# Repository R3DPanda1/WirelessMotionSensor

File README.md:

# Wireless Motion Sensor

A portable all-in-one motion sensor device with Bluetooth connectivity and SD card data logging capabilities, developed as a Bachelor's thesis project at UAS Technikum Wien.

## Overview

This project presents a low-cost, user-friendly wireless motion tracking device designed for measuring acceleration, rotation, and orientation data at 100 Hz using a Bosch BNO055 IMU sensor. The device features wireless communication between two units, local data storage, and an intuitive OLED display interface.

## Key Features

- **High-Speed Motion Capture**: Measures acceleration, rotation, and orientation at 100 Hz
- **Wireless Communication**: Bluetooth Classic connectivity for real-time data sharing between two devices
- **Data Logging**: SD card storage in CSV format for easy data access
- **Clock Synchronization**: Devices can be synchronized by tapping them together (high-g interrupt method)
- **User-Friendly Interface**: 1.3" OLED display with push-button controls
- **Portable Design**: Battery-powered with 3D-printed snap-fit case
- **Multiple Operation Modes**:
  - Fusion Mode (orientation visualization)
  - Temperature Mode
  - Spirit Level Mode
  - Raw Readings Mode

## Hardware Components

### Main Components
- **Microcontroller**: ESP32-WROOM-32
- **IMU Sensor**: Bosch BNO055 (9-DOF with sensor fusion)
- **Display**: SH1106 1.3" OLED (128x64 pixels)
- **Storage**: MicroSD card slot
- **Power**: Li-Ion/Li-Polymer battery with USB-C charging
- **Connectivity**: Bluetooth Classic

### PCB Design

The custom 4-layer PCB features:
- Compact design (96.6mm x 44.4mm x 19.9mm)
- Hand-assembled components
- Compatible with various 0.96" or 1.3" OLED displays
- M5 mounting holes for case integration

### Circuit Schematic

## Case Design

The device is housed in a 3D-printed snap-fit case designed in Autodesk Fusion:

Features:
- Snap-fit assembly (no screws required)
- Integrated battery compartment
- Button and switch caps
- Multi-material printing support for labeling

## Software Architecture

The firmware uses FreeRTOS with seven concurrent tasks:
- **Button Task**: Handles user input
- **Sensor Task**: Reads IMU data and manages clock synchronization
- **Render Task**: Controls OLED display output
- **Bluetooth TX/RX Tasks**: Manages wireless communication
- **SD Card Task**: Handles file operations
- **CSV Task**: Prepares data for logging with write buffer optimization

### Data Recording

- CSV format for easy accessibility
- Buffered writing to reduce SD card wear
- Simultaneous local and remote data logging
- Timestamp synchronization between devices

## Operation Modes

1. **Fusion Mode**: 3D cube visualization of orientation with linear acceleration graph
2. **Temperature Mode**: Display local and remote temperature readings
3. **Spirit Level Mode**: Digital level indicator with tilt angle
4. **Raw Readings Mode**: Real-time graphs of accelerometer, gyroscope, and magnetometer data
5. **Clock Sync Mode**: Synchronize device clocks by tapping them together

## Getting Started

### Hardware Requirements
- Wireless Motion Sensor device
- MicroSD card (formatted as FAT32)
- Li-Ion or Li-Polymer battery (JST 2.54mm connector)
- USB-C cable for charging and programming

### Basic Usage

1. **Power On**: Slide the ON/OFF switch to ON position
2. **Insert SD Card**: Insert a FAT32-formatted microSD card (optional, for data logging)
3. **Connect Devices**: Press the BT button on one device to establish connection
4. **Select Mode**: Press MODE button to cycle through operation modes
5. **Record Data**: Press REC button to start/stop data logging
6. **Sync Clocks**: Press SYNC button (on master device) and tap devices together

### Controls

- **MODE**: Switch between operation modes
- **BT**: Initiate/disconnect Bluetooth connection
- **REC**: Start/stop CSV data logging
- **SYNC**: Begin clock synchronization process (master device only)

## Performance

- **Synchronization Accuracy**: Typically within 5ms
- **Bluetooth Latency**: ~15ms average
- **Data Rate**: 100 Hz for all sensor readings
- **Packet Loss**: ~24% during simultaneous Bluetooth and SD card operations

## Applications

- Motion capture and tracking
- Sports performance analysis
- Gait analysis and rehabilitation
- Robotics and drone motion tracking
- Joint movement studies
- Vibration analysis

## Development

### Build Environment
- Platform: PlatformIO with Arduino framework
- Language: C/C++
- RTOS: FreeRTOS

### PCB Design
- Tool: KiCad
- Manufacturer: Aisler
- Layers: 4 (Signal, Ground, Power, Signal)

### Mechanical Design
- Tool: Autodesk Fusion
- Manufacturing: 3D printing (FDM)

## Project Structure

```
WirelessMotionSensor/
├── src/                    # Source code
├── include/                # Header files
├── KiCad/                  # PCB design files
├── CAD/                    # 3D case design files
├── images/                 # Documentation images
└── platformio.ini          # PlatformIO configuration
```

## Future Improvements

- Enhanced communication protocol (ESP-NOW) for multiple device support
- Optimized code for better performance
- Additional display interfaces
- Live data logging over USB
- Support for more than two connected devices

## License

This project was developed as a Bachelor's thesis at UAS Technikum Wien.

## Author

**Alper Ramadan**
Bachelor of Science in Engineering - Electronics
UAS Technikum Wien, 2024

Supervisor: Stefan Paschek, MSc

## Acknowledgments

Special thanks to:
- UAS Technikum Wien for providing education and resources
- Jakob Frenzel for PCB design guidance
- Adafruit and AZ-Delivery for open-source hardware designs

## References

Based on the Bachelor's thesis: "Development of a Portable Motion Sensor Device with Bluetooth and SD Card Capabilities"

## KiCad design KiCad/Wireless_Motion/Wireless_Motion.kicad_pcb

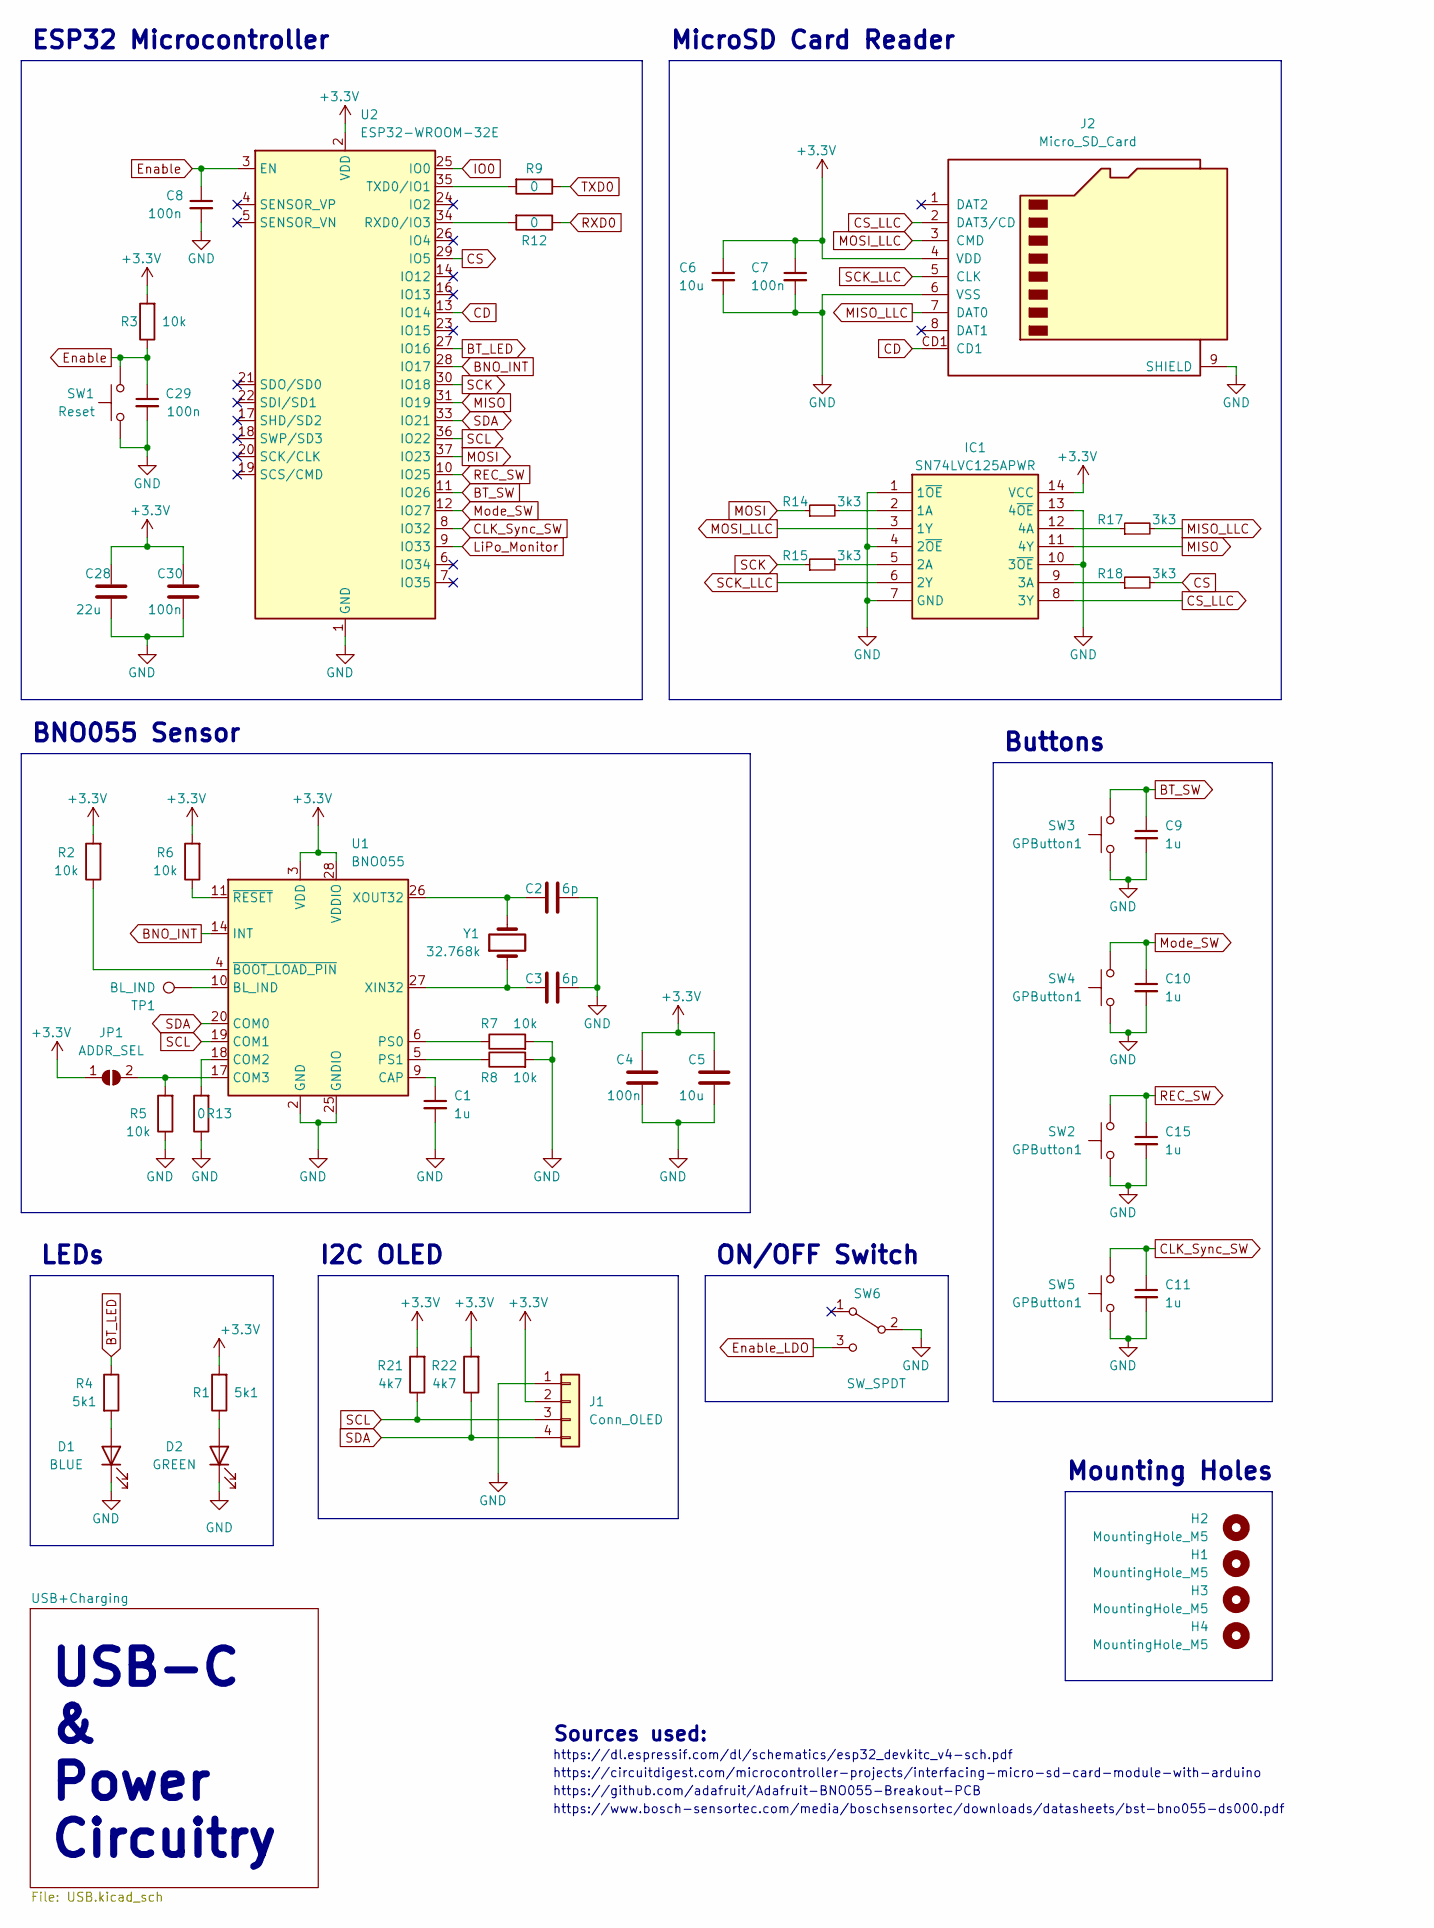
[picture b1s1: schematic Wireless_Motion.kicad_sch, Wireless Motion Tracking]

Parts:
C1, C9, C10, C11, C15: 1u; C_0603_1608Metric
C2, C3: 6p; C_0603_1608Metric; Mouser Part Number 80-CBR06C609C5GAUTO
C4, C7, C8, C29, C30: 100n; C_0603_1608Metric
C5, C6: 10u; C_0603_1608Metric
C28: 22u; C_0603_1608Metric
D1: BLUE; LED_0603_1608Metric; Mouser Part Number 720-LBQ39GL2N2351
D2: GREEN; LED_0603_1608Metric; Mouser Part Number 720-LTQ39GQ1S22515
H1, H2, H3, H4: MountingHole_M5; MountingHole_5.3mm_M5_DIN965
IC1: SN74LVC125APWR; Mouser Part Number 595-SN74LVC125APWR
J1: Conn_OLED; PinHeader_1x04_P2.54mm_Vertical
J2: Micro_SD_Card; MICROSDCARD; Mouser Part Number 909-MICRO-SD-CARD
JP1: ADDR_SEL; SolderJumper-2_P1.3mm_Open_TrianglePad1.0x1.5mm
R1, R4: 5k1; R_0603_1608Metric
R2, R3, R5, R6, R7, R8: 10k; R_0603_1608Metric
R9, R12, R13: 0; R_0603_1608Metric
R14, R15, R17, R18: 3k3; R_0603_1608Metric
R21, R22: 4k7; R_0603_1608Metric
SW1: Reset; SW_SPST_EVQP7C; Mouser Part Number 667-EVQP7C01P
SW2, SW3, SW4, SW5: GPButton1; TL3301TF100QG; Mouser Part Number 612-TL3301SPF260QJ
SW6: SW_SPDT; SW_SPDT_CK-JS102011SAQN; Mouser Part Number 611-JS102011SAQN
TP1: BL_IND; TestPoint_Pad_D1.0mm
U1: BNO055; LGA-28_5.2x3.8mm_P0.5mm; Mouser Part Number 262-BNO055
U2: ESP32-WROOM-32E; ESP32-WROOM-32; Mouser Part Number 356-ESP32WRM320EH3PS
Y1: 32.768k; Crystal_SMD_3215-2Pin_3.2x1.5mm; Mouser Part Number 520-.327-12.5-34QCST

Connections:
+3.3V: C4.1, C5.1, C6.1, C7.1, C28.1, C30.1, IC1.14 (VCC), J1.2, J2.4 (VDD), JP1.1 (A), R1.2, R2.2, R3.2, R6.2, R21.2, R22.2, U1.3 (VDD), U1.28 (VDDIO), U2.2 (VDD); also elsewhere on the board
BNO_INT: U1.14 (INT), U2.28 (IO17)
BT_LED: R4.1, U2.27 (IO16)
BT_SW: C9.1, SW3.1, U2.11 (IO26)
CD: J2.CD1, U2.13 (IO14)
CLK_Sync_SW: C11.1, SW5.1, U2.8 (IO32)
CS: R18.2, U2.29 (IO5)
CS_LLC: IC1.8 (3Y), J2.2 (DAT3/CD)
Enable: C8.1, C29.1, R3.1, SW1.1, U2.3 (EN); also elsewhere on the board
Enable_LDO: SW6.3 (C); also elsewhere on the board
GND: C1.2, C2.2, C3.2, C4.2, C5.2, C6.2, C7.2, C8.2, C9.2, C10.2, C11.2, C15.2, C28.2, C29.2, C30.2, D1.1 (K), D2.1 (K), IC1.1 (1~OE), IC1.4 (2~OE), IC1.7 (GND), IC1.10 (3~OE), IC1.13 (4~OE), J1.1, J2.6 (VSS), J2.9 (SHIELD), R5.1, R7.2, R8.2, R13.1, SW1.2, SW2.2, SW3.2, SW4.2, SW5.2, SW6.2 (B), U1.2 (GND), U1.15 (GNDIO), U1.16 (GNDIO), U1.25 (GNDIO), U2.1 (GND), U2.15 (GND), U2.38 (GND), U2.39 (GND); also elsewhere on the board
IO0: U2.25 (IO0); also elsewhere on the board
LiPo_Monitor: U2.9 (IO33); also elsewhere on the board
MISO: IC1.11 (4Y), U2.31 (IO19)
MISO_LLC: J2.7 (DAT0), R17.2
MOSI: R14.1, U2.37 (IO23)
MOSI_LLC: IC1.3 (1Y), J2.3 (CMD)
Mode_SW: C10.1, SW4.1, U2.12 (IO27)
unnamed: C1.1, U1.9 (CAP)
unnamed: C2.1, U1.26 (XOUT32), Y1.2
unnamed: C3.1, U1.27 (XIN32), Y1.1
unnamed: D1.2 (A), R4.2
unnamed: D2.2 (A), R1.1
unnamed: IC1.2 (1A), R14.2
unnamed: IC1.5 (2A), R15.2
unnamed: IC1.9 (3A), R18.1
unnamed: IC1.12 (4A), R17.1
unnamed: JP1.2 (B), R5.2, U1.17 (COM3)
unnamed: R2.1, U1.4 (~BOOT_LOAD_PIN)
unnamed: R6.1, U1.11 (~RESET)
unnamed: R7.1, U1.6 (PS0)
unnamed: R8.1, U1.5 (PS1)
unnamed: R9.2, U2.35 (TXD0/IO1)
unnamed: R12.2, U2.34 (RXD0/IO3)
unnamed: R13.2, U1.18 (COM2)
unnamed: TP1.1, U1.10 (BL_IND)
REC_SW: C15.1, SW2.1, U2.10 (IO25)
RXD0: R12.1; also elsewhere on the board
SCK: R15.1, U2.30 (IO18)
SCK_LLC: IC1.6 (2Y), J2.5 (CLK)
SCL: J1.3, R21.1, U1.19 (COM1), U2.36 (IO22)
SDA: J1.4, R22.1, U1.20 (COM0), U2.33 (IO21)
TXD0: R9.1; also elsewhere on the board

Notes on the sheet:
I2C OLED
https://www.bosch-sensortec.com/media/boschsensortec/downloads/datasheets/bst-bno055-ds000.pdf
Buttons
ON/OFF Switch
MicroSD Card Reader
Mounting Holes
https://circuitdigest.com/microcontroller-projects/interfacing-micro-sd-card-module-with-arduino
Sources used:
ESP32 Microcontroller
https://dl.espressif.com/dl/schematics/esp32_devkitc_v4-sch.pdf
https://github.com/adafruit/Adafruit-BNO055-Breakout-PCB
BNO055 Sensor
USB-C & Power Circuitry
LEDs

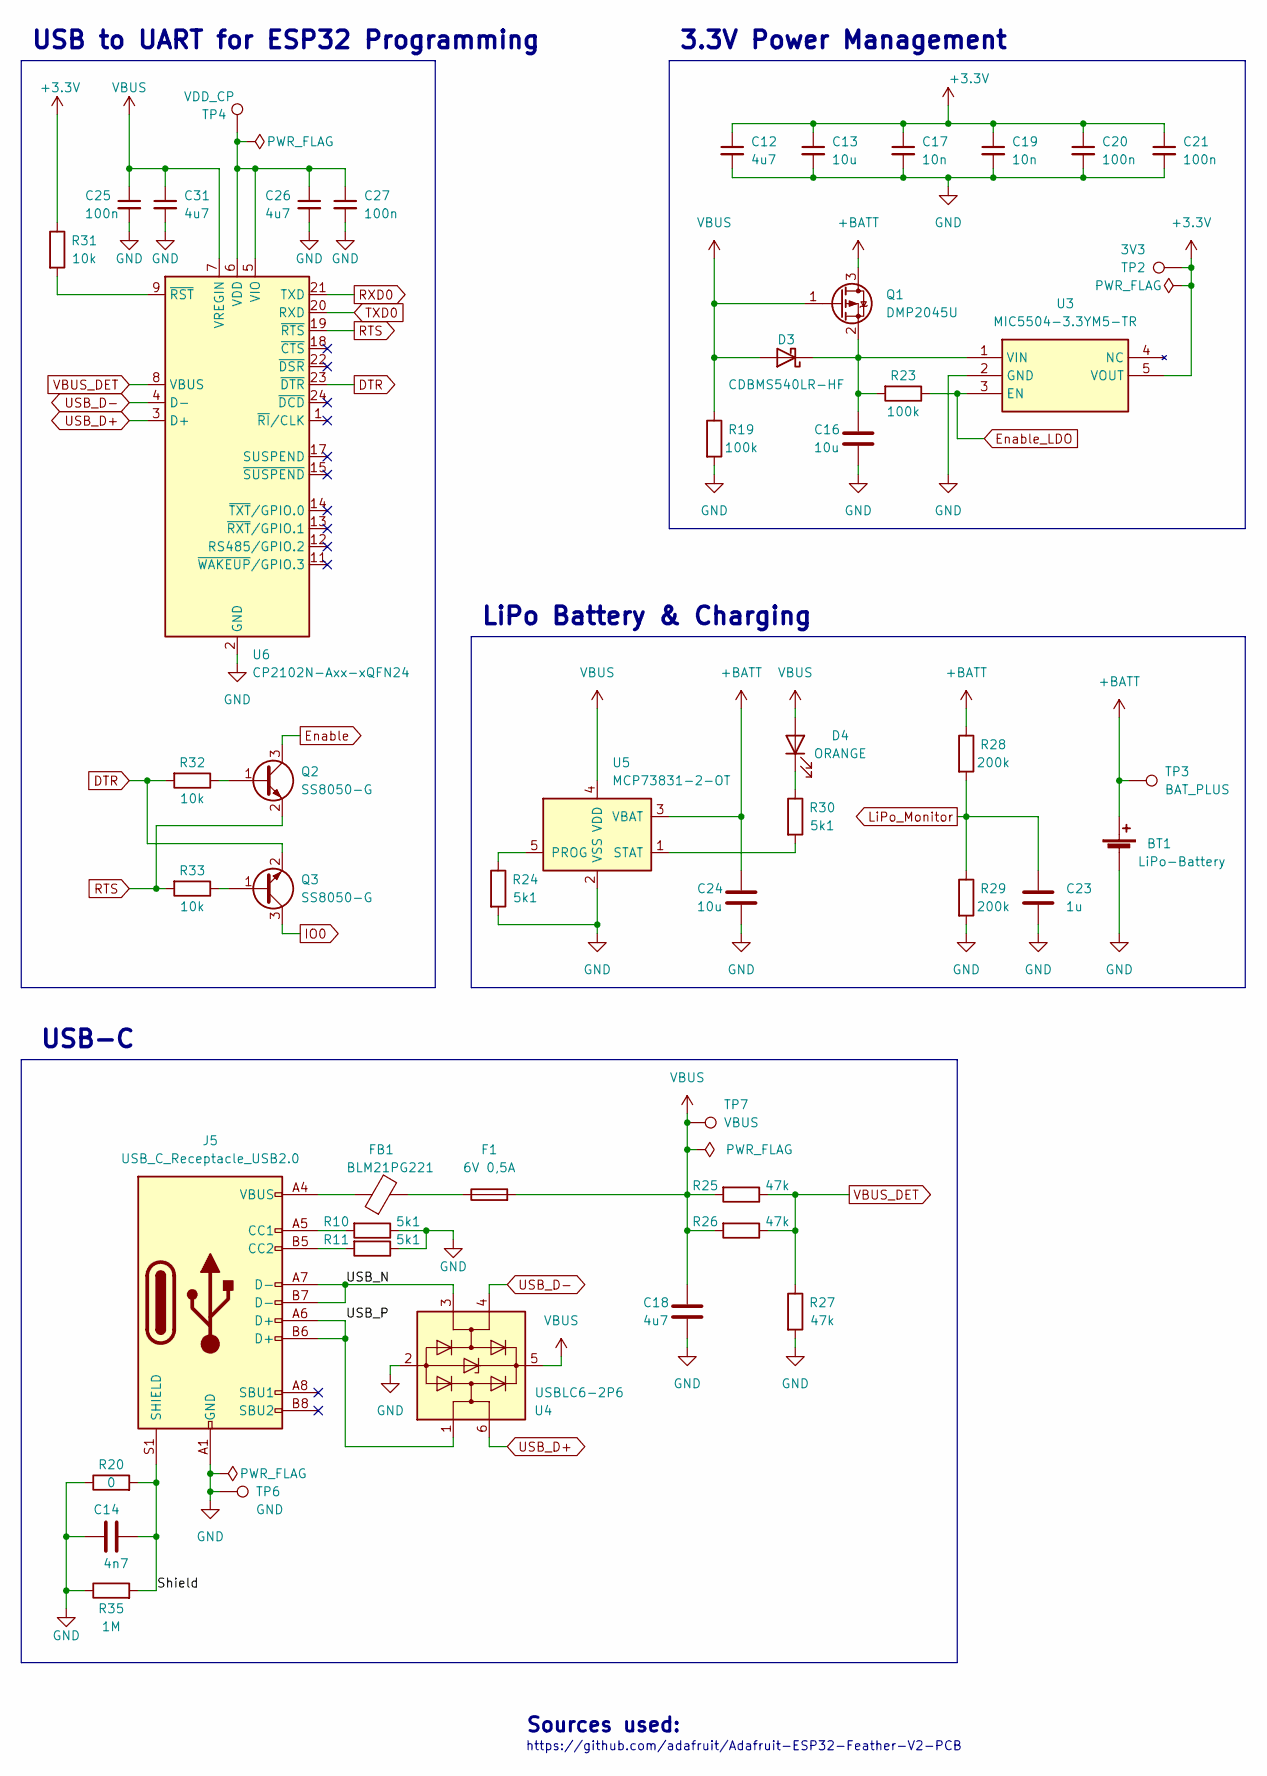
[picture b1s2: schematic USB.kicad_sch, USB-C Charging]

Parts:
BT1: LiPo-Battery; JST_1x02_Horizontal; Mouser Part Number 538-53261-0271
C12, C18, C26, C31: 4u7; C_0603_1608Metric
C13, C16, C24: 10u; C_0603_1608Metric
C14: 4n7; C_1206_3216Metric; Mouser Part Number 80-C1206C472K5R7553
C17, C19: 10n; C_0603_1608Metric
C20, C21, C25, C27: 100n; C_0603_1608Metric
C23: 1u; C_0603_1608Metric
D3: CDBMS540LR-HF; D_SOD-123; Mouser Part Number 750-CDBMS540LR-HF
D4: ORANGE; LED_0603_1608Metric; Mouser Part Number 720-LYQ396P1Q236
F1: 6V 0,5A; Fuse_0603_1608Metric; Mouser Part Number 603-SMD0603B050TF
FB1: BLM21PG221; L_0805_2012Metric; Mouser Part Number 81-BLM21P221SG
J5: USB_C_Receptacle_USB2.0; USB_C_Receptacle_GCT_USB4105-xx-A_16P_TopMnt_Horizontal; Mouser Part Number 640-USB4105-GF-A
Q1: DMP2045U; SOT-23-3; Mouser Part Number 621-DMP2045U-7
Q2, Q3: SS8050-G; SOT-23; Mouser Part Number 750-SS8050-G
R10, R11, R24, R30: 5k1; R_0603_1608Metric
R19, R23: 100k; R_0603_1608Metric
R20: 0; R_0603_1608Metric
R25, R26, R27: 47k; R_0603_1608Metric
R28, R29: 200k; R_0603_1608Metric
R31, R32, R33: 10k; R_0603_1608Metric
R35: 1M; R_0603_1608Metric
TP2: 3V3; TestPoint_Pad_D2.0mm
TP3: BAT_PLUS; TestPoint_Pad_D2.0mm
TP4: VDD_CP; TestPoint_Pad_D1.0mm
TP6: GND; TestPoint_Pad_D2.0mm
TP7: VBUS; TestPoint_Pad_D2.0mm
U3: MIC5504-3.3YM5-TR; SOT95P280X145-5N; Mouser Part Number 998-MIC5504-3.3YM5TR
U4: USBLC6-2P6; SOT-666; Mouser Part Number 511-USBLC6-2P6
U5: MCP73831-2-OT; SOT-23-5; Mouser Part Number MCP73831T-2ACI/OT
U6: CP2102N-Axx-xQFN24; QFN-24-1EP_4x4mm_P0.5mm_EP2.6x2.6mm; Mouser Part Number 634-CP2102NA02QFN24R

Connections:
+3.3V: C12.1, C13.1, C17.1, C19.1, C20.1, C21.1, R31.1, TP2.1, U3.5 (VOUT); also elsewhere on the board
+BATT: BT1.1 (+), C24.1, Q1.3 (D), R28.1, TP3.1, U5.3 (VBAT)
/USB+Charging/Shield: C14.2, J5.S1 (SHIELD), R20.2, R35.2
/USB+Charging/USB_N: J5.A7 (D-), J5.B7 (D-), U4.3 (I/O2)
/USB+Charging/USB_P: J5.A6 (D+), J5.B6 (D+), U4.1 (I/O1)
DTR: Q3.2 (E), R32.2, U6.23 (~DTR)
Enable: Q2.3 (C); also elsewhere on the board
Enable_LDO: R23.1, U3.3 (EN); also elsewhere on the board
GND: BT1.2 (-), C12.2, C13.2, C14.1, C16.2, C17.2, C18.2, C19.2, C20.2, C21.2, C23.2, C24.2, C25.2, C26.2, C27.2, C31.2, J5.A1 (GND), J5.A12 (GND), J5.B1 (GND), J5.B12 (GND), R10.1, R11.1, R19.2, R20.1, R24.2, R27.2, R29.2, R35.1, TP6.1, U3.2 (GND), U4.2 (GND), U5.2 (VSS), U6.2 (GND), U6.25 (GND); also elsewhere on the board
IO0: Q3.3 (C); also elsewhere on the board
LiPo_Monitor: C23.1, R28.2, R29.1; also elsewhere on the board
unnamed: C16.1, D3.1 (K), Q1.2 (S), R23.2, U3.1 (VIN)
unnamed: D4.1 (K), R30.1
unnamed: F1.1, FB1.2
unnamed: FB1.1, J5.A4 (VBUS), J5.A9 (VBUS), J5.B4 (VBUS), J5.B9 (VBUS)
unnamed: J5.A5 (CC1), R10.2
unnamed: J5.B5 (CC2), R11.2
unnamed: Q2.1 (B), R32.1
unnamed: Q3.1 (B), R33.1
unnamed: R24.1, U5.5 (PROG)
unnamed: R30.2, U5.1 (STAT)
unnamed: R31.2, U6.9 (~RST)
unnamed: C26.1, C27.1, TP4.1, U6.5 (VIO), U6.6 (VDD)
RTS: Q2.2 (E), R33.2, U6.19 (~RTS)
RXD0: U6.21 (TXD); also elsewhere on the board
TXD0: U6.20 (RXD); also elsewhere on the board
USB_D+: U4.6 (I/O1), U6.3 (D+)
USB_D-: U4.4 (I/O2), U6.4 (D-)
VBUS: C18.1, C25.1, C31.1, D3.2 (A), D4.2 (A), F1.2, Q1.1 (G), R19.1, R25.2, R26.2, TP7.1, U4.5 (VBUS), U5.4 (VDD), U6.7 (VREGIN)
VBUS_DET: R25.1, R26.1, R27.1, U6.8 (VBUS)

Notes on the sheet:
Sources used:
https://github.com/adafruit/Adafruit-ESP32-Feather-V2-PCB
USB-C
LiPo Battery & Charging
USB to UART for ESP32 Programming
3.3V Power Management

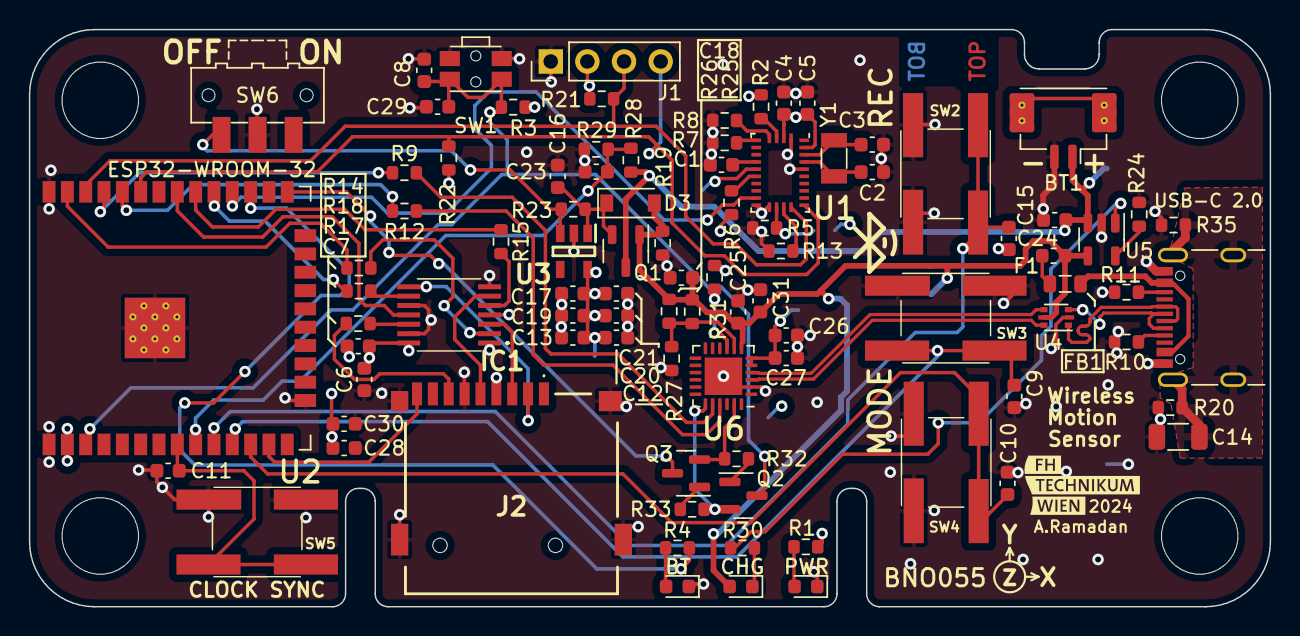
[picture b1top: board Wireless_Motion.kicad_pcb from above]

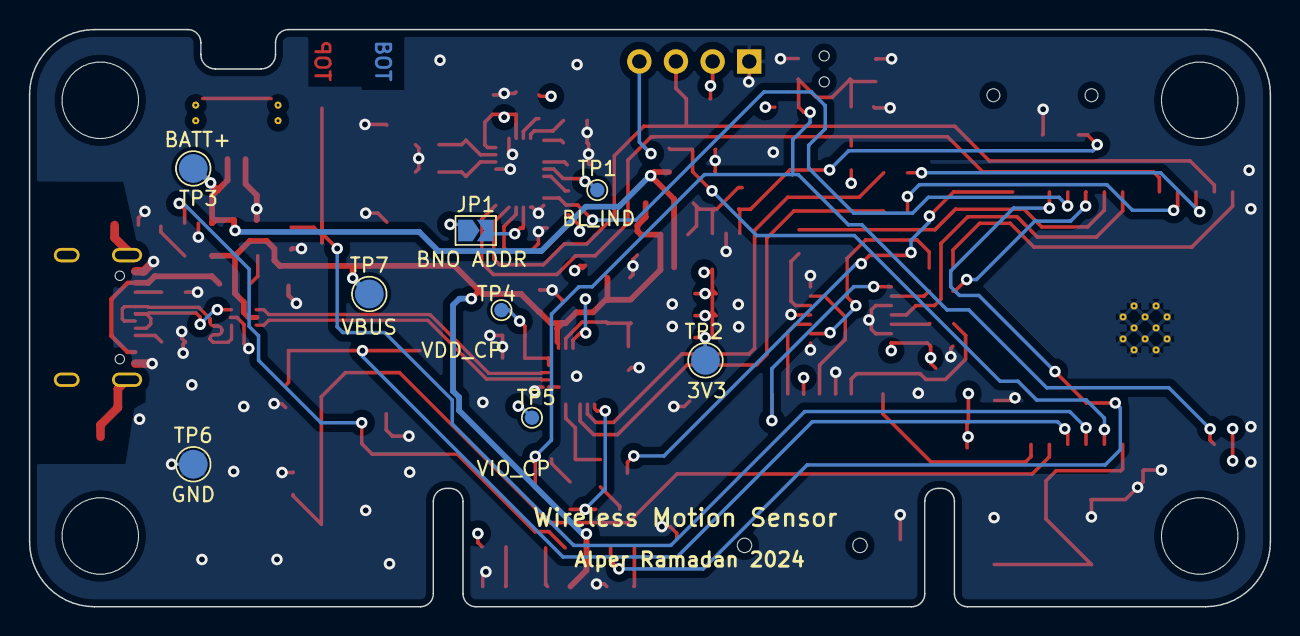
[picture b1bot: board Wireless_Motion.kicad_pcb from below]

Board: 4 copper layers, 86.0 x 40.0 mm, 102 parts (8 on the bottom side), 65 nets.

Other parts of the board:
TP5: VIO_CP; TestPoint_Pad_D1.0mm

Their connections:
+3.3V: TP5.1; also elsewhere on the board

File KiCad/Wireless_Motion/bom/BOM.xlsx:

Bill of Materials for Two Devices
Mouser Parts
Designator | Value | Footprint | Mouser Part Number | Order Unit Price | Quantity | Total
BT1 | LiPo-Battery | JST 1x02 | 538-53261-0271 | 0.40899999999999997 | 2 | 0.81799999999999995
C1,C9,C10,C11,C15,C23 | 1u | 0603 - Inch | 80-C0603C105K4R | 3.9E-2 | 12 | 0.46799999999999997
C12,C18,C26,C31 | 4u7 | 0603 - Inch | 187-CL10A475KQ8NNNC | 9.4E-2 | 8 | 0.752
C14 | 4n7 | 1206 - Inch | 80-C1206C472K5R7553 | 9.2999999999999999E-2 | 2 | 0.186
C17,C19 | 10n | 0603 - Inch | 581-06031C103K | 9.4E-2 | 4 | 0.376
C2,C3 | 6p | 0603 - Inch | 80-CBR06C609C5GAUTO | 9.2999999999999999E-2 | 4 | 0.372
C28 | 22u | 0603 - Inch | 81-GRM188R60J226ME0D | 0.14000000000000001 | 2 | 0.28000000000000003
C4,C7,C8,C20,C21,C25,C27,C29,C30 | 100n | 0603 - Inch | 80-C0603C104J5R | 5.0999999999999997E-2 | 18 | 0.91799999999999993
C5,C6,C13,C16,C24 | 10u | 0603 - Inch | 187-CL10A106MQ8NNNC | 6.7000000000000004E-2 | 10 | 0.67
D1 | BLUE | 0603 - Inch | 720-LBQ39GL2N2351 | 0.33800000000000002 | 2 | 0.67600000000000005
D2 | GREEN | 0603 - Inch | 720-LTQ39GQ1S22515 | 0.33800000000000002 | 2 | 0.67600000000000005
D3 | CDBMS540LR-HF | SOD-123 | 750-CDBMS540LR-HF | 0.36299999999999999 | 2 | 0.72599999999999998
D4 | ORANGE | 0603 - Inch | 720-LYQ396P1Q236 | 0.20499999999999999 | 2 | 0.41
F1 | 6V 0,5A | 0603 - Inch | 603-SMD0603B050TF | 0.188 | 2 | 0.376
FB1 | BLM21PG221 | 0805 - Inch | 81-BLM21P221SG | 0.112 | 2 | 0.224
IC1 | SN74LVC125APWR | SN74LVC125APWR | 595-SN74LVC125APWR | 0.372 | 2 | 0.74399999999999999
J2 | Micro_SD_Card | Micro SD card connector | 909-MICRO-SD-CARD | 0.51200000000000001 | 2 | 1.024
J5 | USB_C_Receptacle_USB2.0 | GCT USB4105-xx-A 16P | 640-USB4105-GF-A | 0.752 | 2 | 1.504
Q1 | DMP2045U | SOT-23-3 | 621-DMP2045U-7 | 0.36299999999999999 | 2 | 0.72599999999999998
Q2,Q3 | SS8050-G | Package_TO_SOT_SMD:SOT-23 | 750-SS8050-G | 0.13 | 4 | 0.52
R1,R4,R10,R11,R24,R30 | 5k1 | 0603 - Inch | 708-RMCF0603FT5K10 | 9.4E-2 | 12 | 1.1280000000000001
R14,R15,R17,R18 | 3k3 | 0603 - Inch | 754-RG1608P-332DT5 | 9.2999999999999999E-2 | 8 | 0.74399999999999999
R19,R23 | 100k | 0603 - Inch | 667-ERJ-3EKF1003V | 9.4E-2 | 4 | 0.376
R2,R3,R5,R6,R7,R8,R31,R32,R33 | 10k | 0603 - Inch | 603-RT0603FRE0710KL | 5.1999999999999998E-2 | 18 | 0.93599999999999994
R21,R22 | 4k7 | 0603 - Inch | 652-CR0603-JW-472ELF | 1.0999999999999999E-2 | 4 | 4.3999999999999997E-2
R25,R26,R27 | 47k | 0603 - Inch | 603-RT0603FRE1347RL | 9.2999999999999999E-2 | 6 | 0.55800000000000005
R28,R29 | 200k | 0603 - Inch | 603-RC0603FR-07200KL | 9.2999999999999999E-2 | 4 | 0.372
R35 | 1M | 0603 - Inch | 603-RC0603FR-071ML | 9.4E-2 | 2 | 0.188
R9,R12,R13,R20 | 0 | 0603 - Inch | 603-RC0603FR-070RL | 9.4E-2 | 8 | 0.752
SW1 | Reset | EVQP7 | 667-EVQP7C01P | 0.27300000000000002 | 2 | 0.54600000000000004
SW2,SW3,SW4,SW5 | GPButton1 | TL3301 | 612-TL3301SPF260QJ | 0.24399999999999999 | 8 | 1.952
SW6 | SW_SPDT | SPDT | 611-JS102011SAQN | 0.62 | 2 | 1.24
U1 | BNO055 | BNO055 | 262-BNO055 | 11.46 | 2 | 22.92
U2 | ESP32-WROOM-32E | ESP32-WROOM-32 | 356-ESP32WRM320EH3PS | 2.54 | 2 | 5.08
U3 | MIC5504-3.3YM5-TR | SOT-95 | 998-MIC5504-3.3YM5TR | 0.15 | 2 | 0.3
U4 | USBLC6-2P6 | SOT-666 | 511-USBLC6-2P6 | 0.42799999999999999 | 2 | 0.85599999999999998
U5 | MCP73831-2-OT | SOT-23-5 | MCP73831T-2ACI/OT | 0.64200000000000002 | 2 | 1.284
U6 | CP2102N-Axx-xQFN24 | CP2102 | 634-CP2102NA02QFN24R | 3.22 | 2 | 6.44
Y1 | 32.768k | SMD_3215-2Pin_3.2x1.5mm | 520-.327-12.5-34QCST | 0.91100000000000003 | 2 | 1.8220000000000001
 |  |  |  |  | Total: | 59.983999999999995
Other Parts
Part | Purchase link |  |  | Order Unit Price | Quantity | Total
OLED Display | https://www.amazon.de/dp/B07V9SLQ6W |  |  | 6.39 | 2 | 12.78
Battery | https://www.amazon.de/dp/B087LTZW61 |  |  | 6.0475000000000003 | 2 | 12.095000000000001
 |  |  |  |  | Total: | 24.875
Aisler PCB Order
Product |  |  |  | Order Unit Price | Order Quantity | Total
Beautiful Board HD 4L |  |  |  | 8.0233333299999998 | 3 | 24.07
Stellar Stencil |  |  |  | 8.27 | 1 | 8.27
 |  |  |  |  | Total for 3 PCBs: | 32.340000000000003
 |  |  | Grand Total for Two Devices (Untaxed) |  |  | 117.199
 |  |  | Grand Total for Two Devices (Taxed 20%) |  |  | 140.6388

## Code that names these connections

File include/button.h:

#ifndef BUTTON_H
#define BUTTON_H

#include <Arduino.h>
#include "commons.h"

#define BT_SW_PIN 26       // Pin number for Bluetooth switch
#define REC_SW_PIN 25      // Pin number for Record switch
#define MODE_SW_PIN 27     // Pin number for Mode switch
#define CLK_SYNC_SW_PIN 32 // Pin number for Clock Sync switch

/**
 * @brief Task function for handling button inputs
 * 
 * @param pvParameters Pointer to the parameters passed to the task
 */
void buttonTask(void* pvParameters);

extern TaskHandle_t buttonTaskHandle;

#endif // BUTTON_H

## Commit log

2024-05-01 less code by using imu namespace
2024-05-01 mode managing
2024-05-05 working bluetooth messaging
2024-05-05 added commons.h
2024-05-06 working bluetooth
2024-05-07 fixed bt, added more graphics
2024-05-07 finished first mode
2024-05-07 mode changing and bt fixes
2024-05-08 working async sd card
2024-05-12 sd card improvements
2024-05-15 temp mode, improvements
2024-05-18 spirit level mode
2024-05-18 battery icom
2024-05-18 battery icon improvement
2024-05-19 clock syncing added
2024-05-19 renamed LinacQuad to Fusion
2024-05-19 changed Fusion ID
2024-05-19 Added more notifications
2024-05-20 sd card code rewrite
2024-05-20 relative orientation implemented
2024-05-22 renamed orientation to rotation
2024-05-22 clk sync master check added
2024-05-22 relative rotatio correctly implemented
2024-05-22 sync mode notifications only on shown on master
2024-05-30 improved time sync and other improvements
2024-05-31 added raw readings mode
2024-06-02 improved naming
2024-06-07 IMU data semaphores
2024-06-07 KiCad files
2024-06-07 3D printed case files
2024-06-09 added comments
2025-12-06 Added a README
